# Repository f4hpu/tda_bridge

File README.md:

<h1 align="center">The tda_bridge Project</h1>

[ en Français](./documentation/README_fr.md)

This repository contains a [KiCAD 6.0.9](https://www.kicad.org/) project for an electronics board (hardware).

This electronics board is a bridgeable audio stereo amplifier, based on a pair of TDA7293 chips.

## Concept

The schematics around the TDA7293 was inspired by ST [datasheet](http://www.st.com/web/en/resource/technical/document/datasheet/CD00001887.pdf) and improved by [Francis Ibre for better sound.](http://www.cinetson.org/phpBB3/electronique-f13/1er-ampli-diy-question-diverse-t17238-30.html)

It includes onboard the same card both a power Supply and a watchdog to protect the loudspeakers against continuous voltage.

In addition, this stereo amplifier could easily be converted into a high power mono amplifier (bridge mode) by soldering R26, removing R28 and shunting R25.

## Historical background

A first implementation was made by authors (F4HPU and F4GUX) as reported in [Fangorn's blog](http://fangorn.over-blog.org/article-23233481.html).

Then, a first design was started using [Eagle (free version)](https://www.autodesk.fr/products/eagle/free-download) in 2014. The design then stoped as the size of the board was beyond the limitation of the free version of the CAD software.

Fortunately, in the mean time KiCAD team upgraded highly this wonderful tool and the project could be switched seamlessly to KiCAD 6.0.9.

For this historical reason, the 3D view of the card is not working well as there was no 3D view for the libraries converted from Eagle.

## Technical information

| Characteristics       | Value                              |
| --------------------- | ---------------------------------- |
| Output Power in 8 ohm | 2x70W (stereo) or 1x280W (bridged) |
| Circuit Dimensions    | 176.5mm x 128.5 mm                 |

## Building a tda_bridge card

You have two options wether you wish to build the project as is (i.e. without using KiCAD), or tweak it to fit to your needs:

1. Download the [latest release](https://github.com/f4hpu/tda_bridge/releases/download/v0.0.0-alpha/fabrication.tar.gz) of this project "as is". This archive encloses a BOM (list of components), a directory with the gerber files, and useful pdf files.
2. or git clone this repo (or even download a zip of the directory) and install [KiCAD 6.0.9](https://www.kicad.org/) to open the project. From here, you can tweak the schematics, the routing and generate your Gerber files.

Once you have the gerber files, you can build the 2-sided PCB.

In case you wish to use a single sided PCB, authors guess that's possible if you put straps for the few missing connections. The ground plane effect may be less effective and the noise floor may rise up a little.

KiCAD offers the possibility to print a BOM to buy everything you need for the card by itself. But of course you may want to add some other stuffs, like the power supply transformer, a power switch, a potentiometer to control the output level, a box, a big heatsink (around ~0.4deg/W) for both the TDA7293's and the Diode's. You may find some inspiration in 
[Fangorn's blog - article 1](http://fangorn.over-blog.org/article-22214740.html)/[article 2](http://fangorn.over-blog.org/article-23233481.html), or [Erriez Guitar Amplifier](https://github.com/Erriez/DualTDA7293PowerAmplifier)

### Continuous voltage protection

A continuous voltage may arm the speaker. For this reason, authors included a circuit continuously watching both left and right outputs. In case of any failure both left and right speakers are disconnected.

The system is a custom design by F4HPU and F4GUX, which behavior was simulated using [LTSpice](https://www.analog.com/en/design-center/design-tools-and-calculators/ltspice-simulator.html).

A Jumper was included to select between using this watchdog, or bypassing it.

### Bridge mode

The Bridge mode is a special mode where the two lines of the stereo amplifier are used simultaneously to drive a single loudspeaker. Simply speaking, for an input signal V_in, left output is (A.V_in), while right output is (-A.V_in), therefore output between left and right is four times higher (as voltage is twice higher).

If you foresee to use this amplifier as a _stereo amplifier_ you need to: remove R26, solder R28, solder R25. In this case, the speakers shall be connected between ground and output_left for left speaker, and ground and output_right for right speaker.

But if you foresee to use this amplifier as a _high power mono amplifier_ you need to: solder R26, remove R28, replace R25 by a shunt. In this case, the speaker shall be connected between output_left and output_right.

## Licencing and Property

The design was made by F4HPU and F4GUX, who are [French Amateur Radio Operators.](https://www.r-e-f.org/)

Both Schematics and PCB are licensed under [CERN-OHL-P version 2](https://cern-ohl.web.cern.ch/home). 

IMPORTANT NOTE: CURRENT DESIGN HAS NEVER BEEN TESTED FOR REAL YET, SO BE CAREFULL, USE AT YOUR OWN RISKS.

For this reason, you are highly encouraged to check each functionnality step by step.

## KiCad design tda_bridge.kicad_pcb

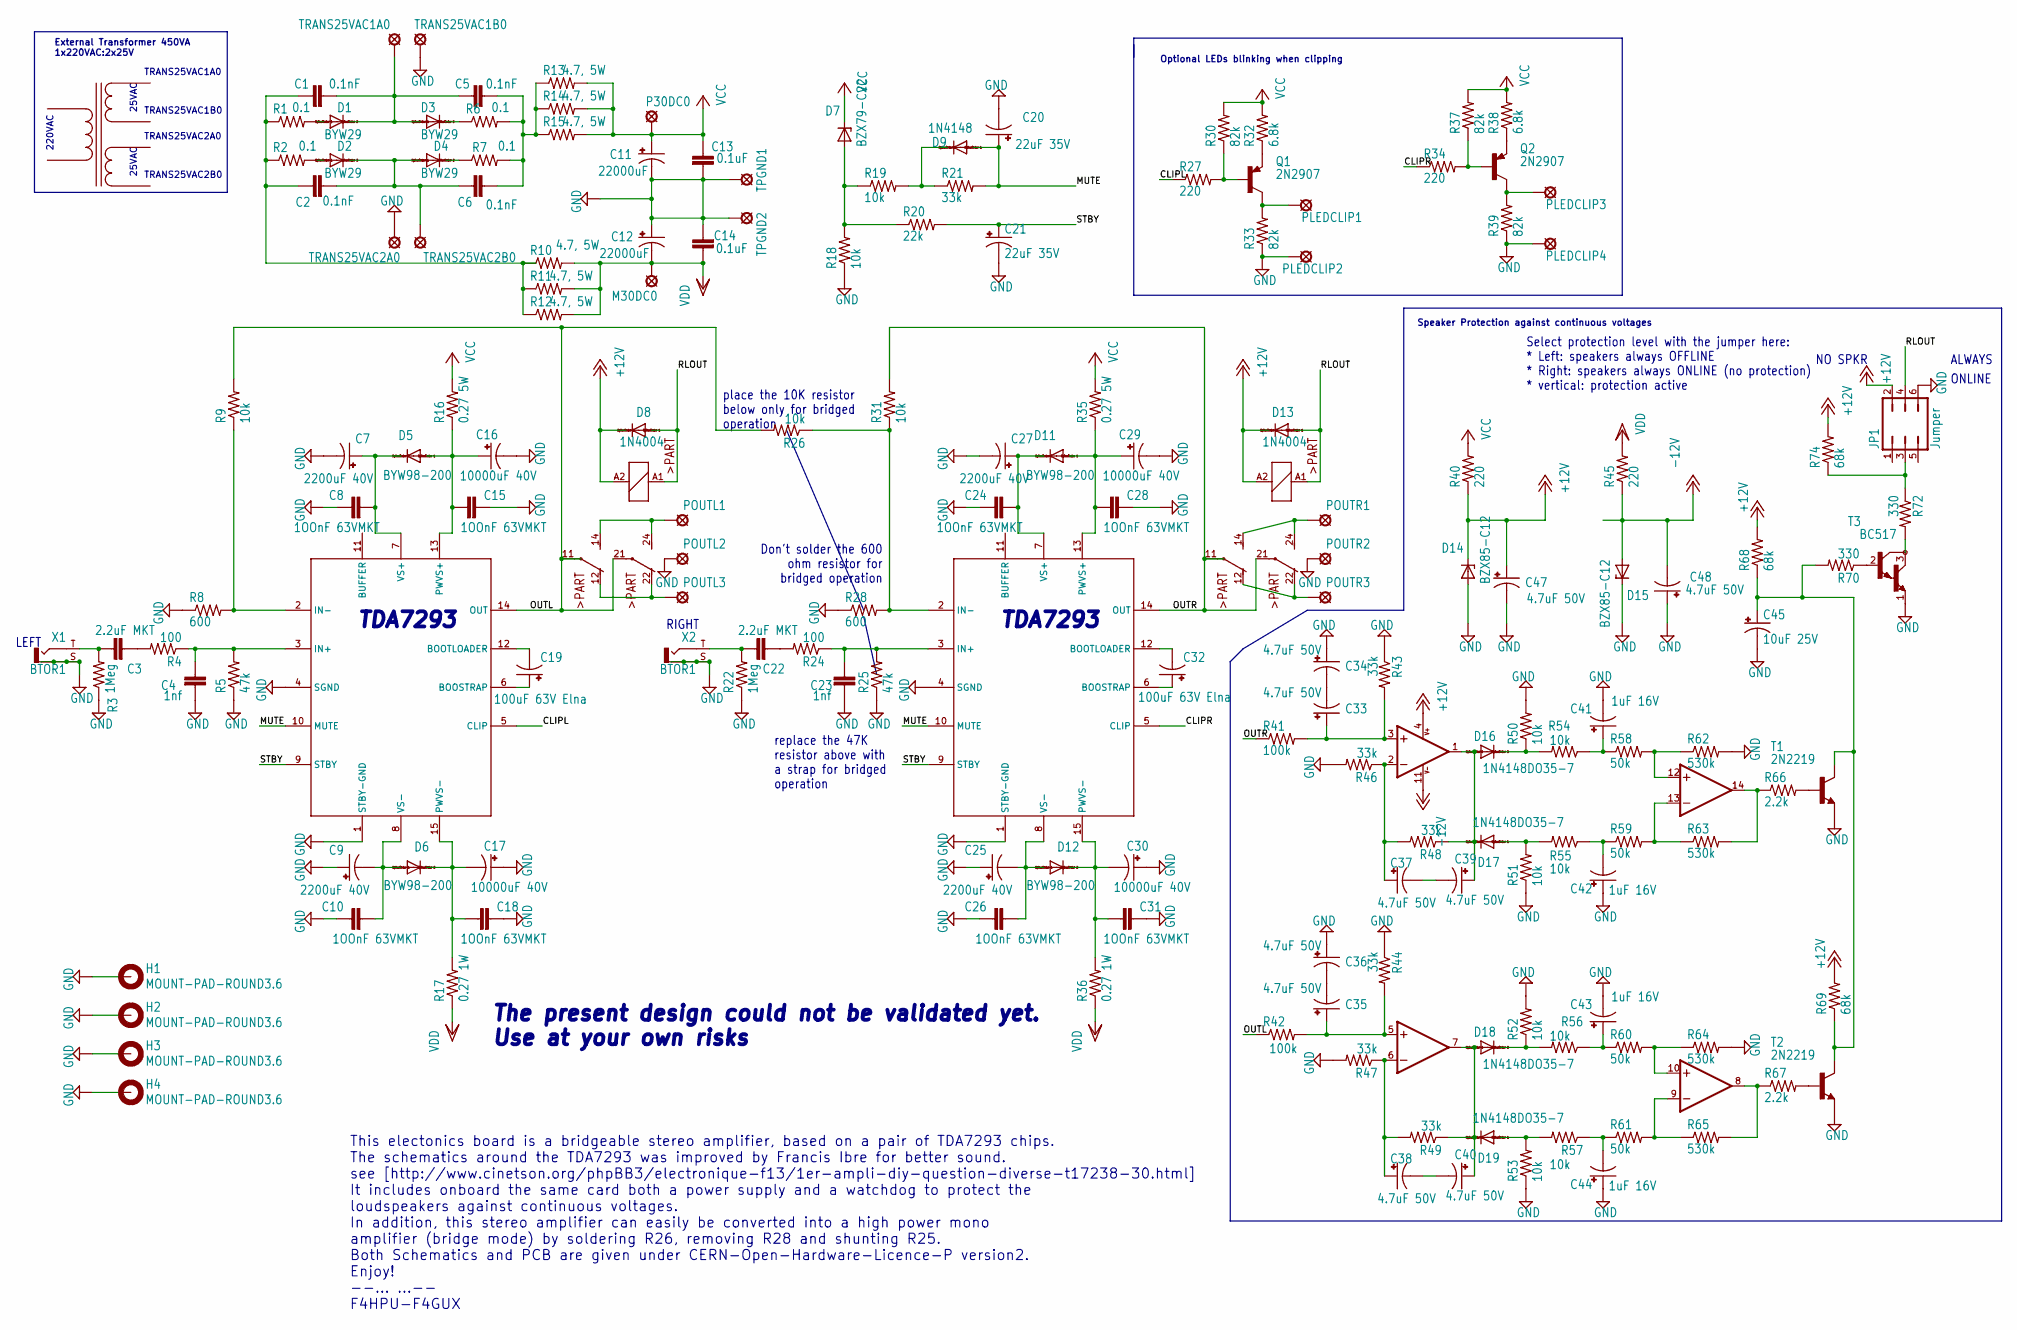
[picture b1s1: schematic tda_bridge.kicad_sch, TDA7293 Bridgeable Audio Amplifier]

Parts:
C1, C2, C5, C6: 0.1nF; C5B2.5
C3, C22: C075-063X106
C4, C23: C050-030X075
C7, C9, C25, C27: 2200uF 40V; E7,5-18
C8, C10, C15, C18, C24, C26, C28, C31: 1OOnF 63VMKT; C050-025X075
C11, C12: 22000uF; EB35D
C13, C14: 0.1uF; C22.5B6
C16, C17, C29, C30: 10000uF 40V; EB30D
C19, C32: 100uF 63V Elna; E5-13
C20, C21: 22uF 35V; E2-5
C33, C34, C35, C36, C37, C38, C39, C40, C47, C48: 4.7uF 50V; E1,8-4
C41, C42, C43, C44: 1uF 16V; E1,8-4
C45: 10uF 25V; E1,8-4
D1, D2, D3, D4: BYW29; DO220S
D5, D6, D11, D12: BYW98-200; F126-10
D7, D14, D15: DO41Z10
D8, D13: 1N4004; DO41-10
D9: 1N4148; DO35-10
D16, D17, D18, D19: 1N4148DO35-7; DO35-7
H1, H2, H3, H4: MOUNT-PAD-ROUND3.6; 3,6-PAD
IC1, IC2: TDA7293V; MULTIWATT15V
IC3: TL084; DIL14
JP1: Jumper; JP3Q
K1, K3: FINDER-30.22
M30DC0: SE13
P30DC0: SE13
PLEDCLIP1, PLEDCLIP2, PLEDCLIP3, PLEDCLIP4: SE13
POUTL1, POUTL2, POUTL3: SE13
POUTR1, POUTR2, POUTR3: SE13
Q1, Q2: 2N2907; TO18
R1, R2, R6, R7: 0.1; 0309_10
R3, R22: 1Meg; 0207_7
R4, R24: 100; 0207_7
R5, R25: 47k; 0207_7
R8, R28: 600; 0207_7
R9, R31: 10k; 0617_22
R10, R11, R12, R13, R14, R15: 4.7, 5W; VTA52
R16, R35: 0.27 5W; 0411_15
R17, R36: 0.27 1W; 0411_15
R18, R19, R26, R50, R51, R52, R53, R54, R55, R56, R57: 10k; 0207_7
R20: 22k; 0207_12
R21, R48, R49: 33k; 0207_7
R27, R34, R45: 220; 0207_7
R30, R33, R37, R39: 82k; 0207_7
R32, R38: 6.8k; 0207_7
R40: 220; 0207_12
R41: 100k; 0207_7
R42: 100k; 0207_12
R43, R44, R46, R47: 33k; 0207_2V
R58, R59, R60, R61: 50k; 0207_7
R62, R63, R64, R65: 530k; 0207_7
R66: 2.2k; 0207_7
R67: 2.2k; 0207_12
R68, R69, R74: 68k; 0207_7
R70, R72: 330; 0207_7
T1, T2: 2N2219; TO5
T3: BC517; TO92
T4: Transformer_1P_2S
TPGND1, TPGND2: SE13
TRANS25VAC1A0, TRANS25VAC1B0, TRANS25VAC2A0, TRANS25VAC2B0: SE13
X1, X2: BTOR1

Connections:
+12V: C47.+, D8.C, D13.C, D14.C, IC3.4 (V+), JP1.2, K1.A2 (2), K3.A2 (2), R40.1, R68.2, R69.2, R74.2
-12V: C48.-, D15.A, IC3.11 (V-), R45.1
/CLIPL: IC1.5 (CLIP), R27.1
/CLIPR: IC2.5 (CLIP), R34.1
/MUTE: C20.+, D9.A, IC1.10 (MUTE), IC2.10 (MUTE), R21.2
/OUTL: IC1.14 (OUT), K1.11, K1.21, R9.2, R26.2, R42.1
/OUTR: IC2.14 (OUT), K3.11, K3.21, R31.2, R41.1
/RLOUT: D8.A, D13.A, JP1.4, K1.A1 (1), K3.A1 (1)
/STBY: C21.+, IC1.9 (STBY), IC2.9 (STBY), R20.2
GND: C4.2, C7.-, C8.1, C9.+, C10.1, C11.-, C12.+, C13.2, C14.2, C15.1, C16.-, C17.+, C18.1, C20.-, C21.-, C23.2, C24.1, C25.+, C26.1, C27.-, C28.1, C29.-, C30.+, C31.1, C34.+, C36.+, C41.-, C42.+, C43.-, C44.+, C45.-, C47.-, C48.+, D14.A, D15.C, H1.B3,6 (MOUNT), H2.B3,6 (MOUNT), H3.B3,6 (MOUNT), H4.B3,6 (MOUNT), IC1.1 (STBY-GND), IC1.4 (SGND), IC2.1 (STBY-GND), IC2.4 (SGND), JP1.6, PLEDCLIP2.MP, PLEDCLIP4.MP, POUTL2.MP, POUTR2.MP, R3.1, R5.1, R8.1, R18.1, R22.1, R25.1, R28.1, R33.1, R39.1, R43.1, R44.1, R46.2, R47.2, R50.2, R51.1, R52.2, R53.1, R62.2, R64.2, T1.1 (E), T2.1 (E), T3.1 (E), TPGND1.MP, TPGND2.MP, TRANS25VAC1B0.MP, TRANS25VAC2A0.MP, X1.S (2), X1.S@1 (2@1), X1.S@2 (2@2), X1.S@3 (2@3), X2.S (2), X2.S@1 (2@1), X2.S@2 (2@2), X2.S@3 (2@3)
unnamed: C1.1, C2.1, R1.1, R2.1, R10.1, R11.1, R12.1
unnamed: C1.2, C5.1, D1.C, D3.A, TRANS25VAC1A0.MP
unnamed: C2.2, C6.1, D2.C, D4.A, TRANS25VAC2B0.MP
unnamed: C3.1, R3.2, X1.T (1)
unnamed: C3.2, R4.2
unnamed: C4.1, IC1.3 (IN+), R4.1, R5.2
unnamed: C5.2, C6.2, R6.2, R7.2, R13.1, R14.1, R15.1
unnamed: C7.+, C8.2, D5.C, IC1.7 (VS+)
unnamed: C9.-, C10.2, D6.A, IC1.8 (VS-)
unnamed: C15.2, C16.+, D5.A, IC1.13 (PWVS+), R16.1
unnamed: C17.-, C18.2, D6.C, IC1.15 (PWVS-), R17.2
unnamed: C19.+, IC1.6 (BOOSTRAP)
unnamed: C19.-, IC1.12 (BOOTLOADER)
unnamed: C22.1, R22.2, X2.T (1)
unnamed: C22.2, R24.2
unnamed: C23.1, IC2.3 (IN+), R24.1, R25.2
unnamed: C24.2, C27.+, D11.C, IC2.7 (VS+)
unnamed: C25.-, C26.2, D12.A, IC2.8 (VS-)
unnamed: C28.2, C29.+, D11.A, IC2.13 (PWVS+), R35.1
unnamed: C30.-, C31.2, D12.C, IC2.15 (PWVS-), R36.2
unnamed: C32.+, IC2.6 (BOOSTRAP)
unnamed: C32.-, IC2.12 (BOOTLOADER)
unnamed: C33.+, IC3.3 (+IN), R41.2, R43.2
unnamed: C33.-, C34.-
unnamed: C35.+, IC3.5 (+IN), R42.2, R44.2
unnamed: C35.-, C36.-
unnamed: C37.+, IC3.2 (-IN), R46.1, R48.2
unnamed: C37.-, C39.-
unnamed: C38.+, IC3.6 (-IN), R47.1, R49.2
unnamed: C38.-, C40.-
unnamed: C39.+, D16.A, D17.C, IC3.1 (OUT), R48.1
unnamed: C40.+, D18.A, D19.C, IC3.7 (OUT), R49.1
unnamed: C41.+, R54.1, R58.1
unnamed: C42.-, R55.1, R59.1
unnamed: C43.+, R56.1, R60.1
unnamed: C44.-, R57.1, R61.1
unnamed: D1.A, R1.2
unnamed: D2.A, R2.2
unnamed: D3.C, R6.1
unnamed: D4.C, R7.1
unnamed: D7.A, R18.2, R19.1, R20.1
unnamed: D9.C, R19.2, R21.1
unnamed: D16.C, R50.1, R54.2
unnamed: D17.A, R51.2, R55.2
unnamed: D18.C, R52.1, R56.2
unnamed: D19.A, R53.2, R57.2
unnamed: IC1.2 (IN-), R8.2, R9.1
unnamed: IC2.2 (IN-), R26.1, R28.2, R31.1
unnamed: IC3.8 (OUT), R65.2, R67.1
unnamed: IC3.9 (-IN), R61.2, R65.1
unnamed: IC3.10 (+IN), R60.2, R64.1
unnamed: IC3.12 (+IN), R58.2, R62.1
unnamed: IC3.13 (-IN), R59.2, R63.1
unnamed: IC3.14 (OUT), R63.2, R66.1
unnamed: JP1.3, R72.1, R74.1
unnamed: K1.12 (O), K1.22 (O), POUTL3.MP
unnamed: K1.14 (S), K1.24 (S), POUTL1.MP
unnamed: K3.12 (O), K3.22 (O), POUTR3.MP
unnamed: K3.14 (S), K3.24 (S), POUTR1.MP
unnamed: PLEDCLIP1.MP, Q1.3 (C), R33.2
unnamed: PLEDCLIP3.MP, Q2.3 (C), R39.2
unnamed: Q1.1 (E), R32.1
unnamed: Q1.2 (B), R27.2, R30.1
unnamed: Q2.1 (E), R38.1
unnamed: Q2.2 (B), R34.2, R37.1
unnamed: R66.2, T1.2 (B)
unnamed: R67.2, T2.2 (B)
unnamed: C45.+, R68.1, R69.1, R70.2, T1.3 (C), T2.3 (C)
unnamed: R70.1, T3.2 (B)
unnamed: R72.2, T3.3 (C)
VCC: C11.+, C13.1, D7.C, P30DC0.MP, R13.2, R14.2, R15.2, R16.2, R30.2, R32.2, R35.2, R37.2, R38.2, R40.2
VDD: C12.-, C14.1, M30DC0.MP, R10.2, R11.2, R12.2, R17.1, R36.1, R45.2

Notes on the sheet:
25VAC
TRANS25VAC1A0
ALWAYS
Optional LEDs blinking when clipping
TDA7293
ONLINE
NO SPKR
This electonics board is a bridgeable stereo amplifier, based on a pair of TDA7293 chips. The schematics around the TDA7293 was improved by Francis Ibre for better sound. see [http://www.cinetson.org/phpBB3/electronique-f13/1er-ampli-diy-question-diverse-t17238-30.html] It includes onboard the same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
TRANS25VAC1B0
LEFT
Don't solder the 600 ohm resistor for bridged operation
220VAC
The present design could not be validated yet. Use at your own risks
TRANS25VAC2B0
place the 10K resistor below only for bridged operation
RIGHT
Select protection level with the jumper here: * Left: speakers always OFFLINE * Right: speakers always ONLINE (no protection) * vertical: protection active
Speaker Protection against continuous voltages
TRANS25VAC2A0
replace the 47K resistor above with a strap for bridged operation
External Transformer 450VA 1x220VAC:2x25V

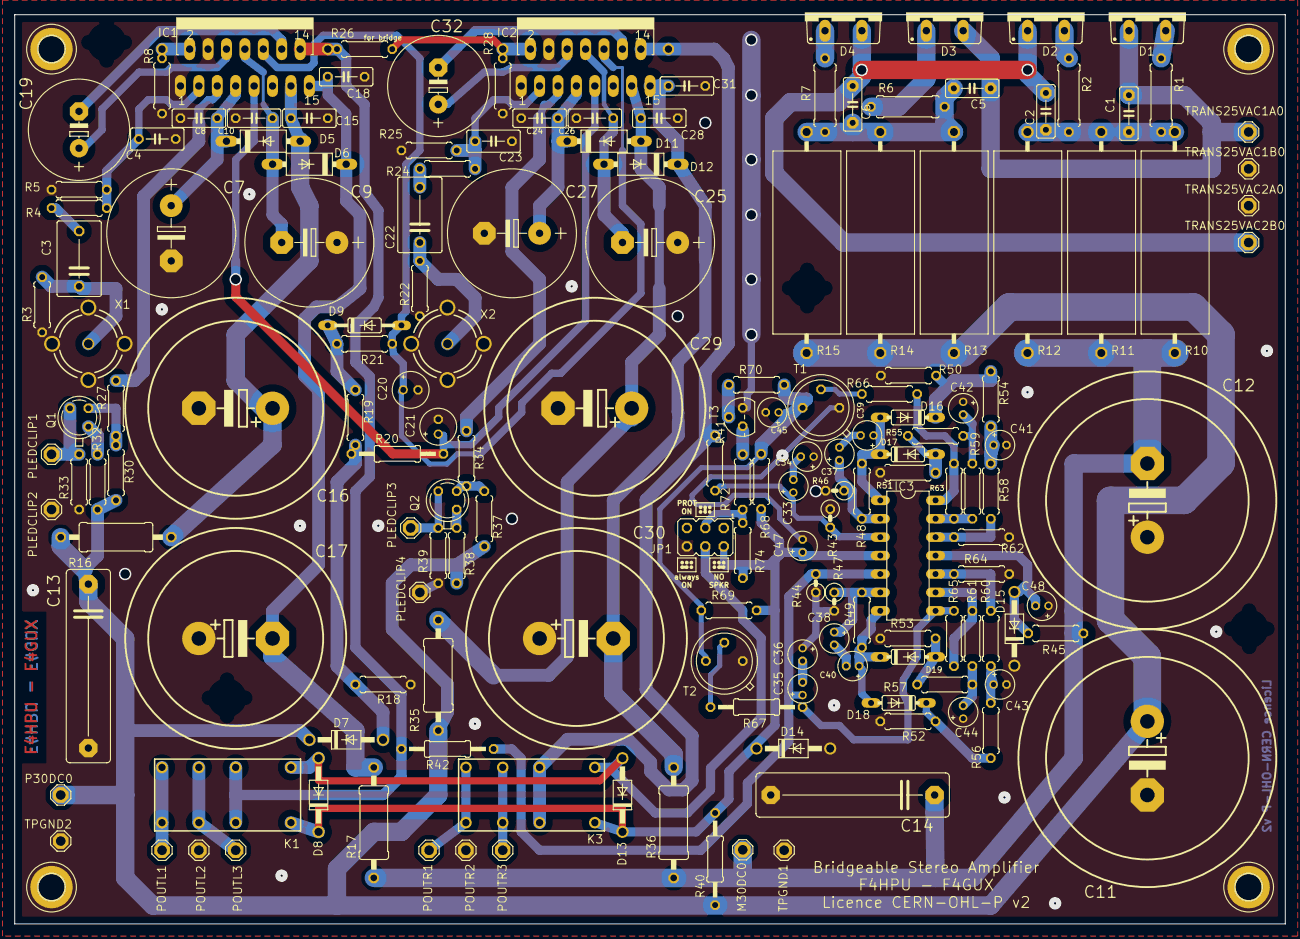
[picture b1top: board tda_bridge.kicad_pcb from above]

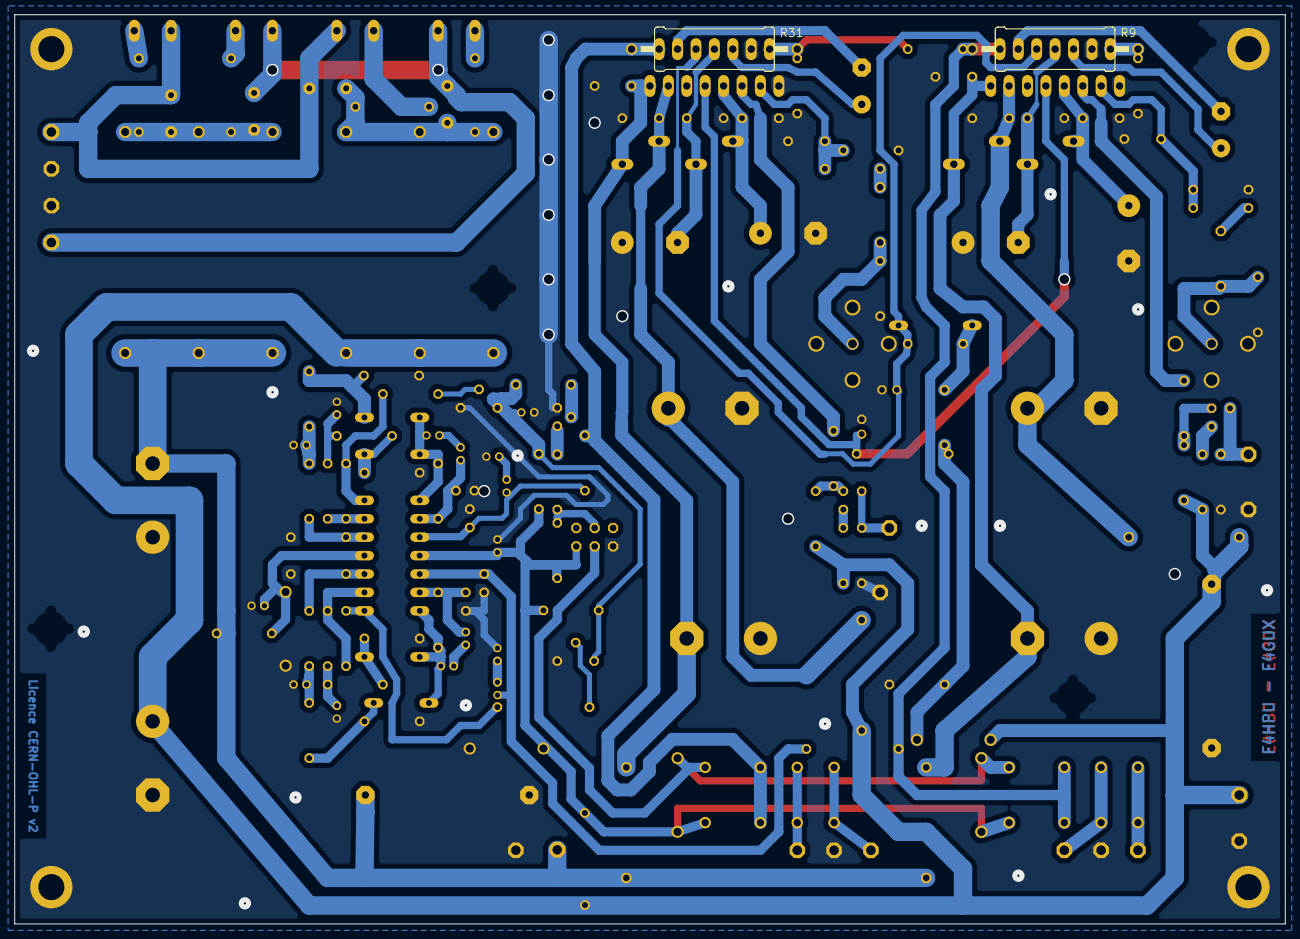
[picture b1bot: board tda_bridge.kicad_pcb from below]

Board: 2 copper layers, 175.2 x 125.4 mm, 170 parts (2 on the bottom side), 82 nets.

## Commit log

2022-11-02 corrected typos in README
2022-11-03 prepared release v0.0.0-alpha
2022-11-03 added fabrication.tar.gz to gitignore to avoid adding the release files in the code
2022-11-03 added version badge
2022-11-04 created a devel branch dedicated to advances before releases in master
2022-11-04 added badge for licence
2022-11-04 detailed release archive content

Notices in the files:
README.md:
Licence CERN OHL-P v2
tda_bridge.kicad_pcb:
Both Schematics and PCB are given under CERN-Open-Hardware-Licence-P version 2.
